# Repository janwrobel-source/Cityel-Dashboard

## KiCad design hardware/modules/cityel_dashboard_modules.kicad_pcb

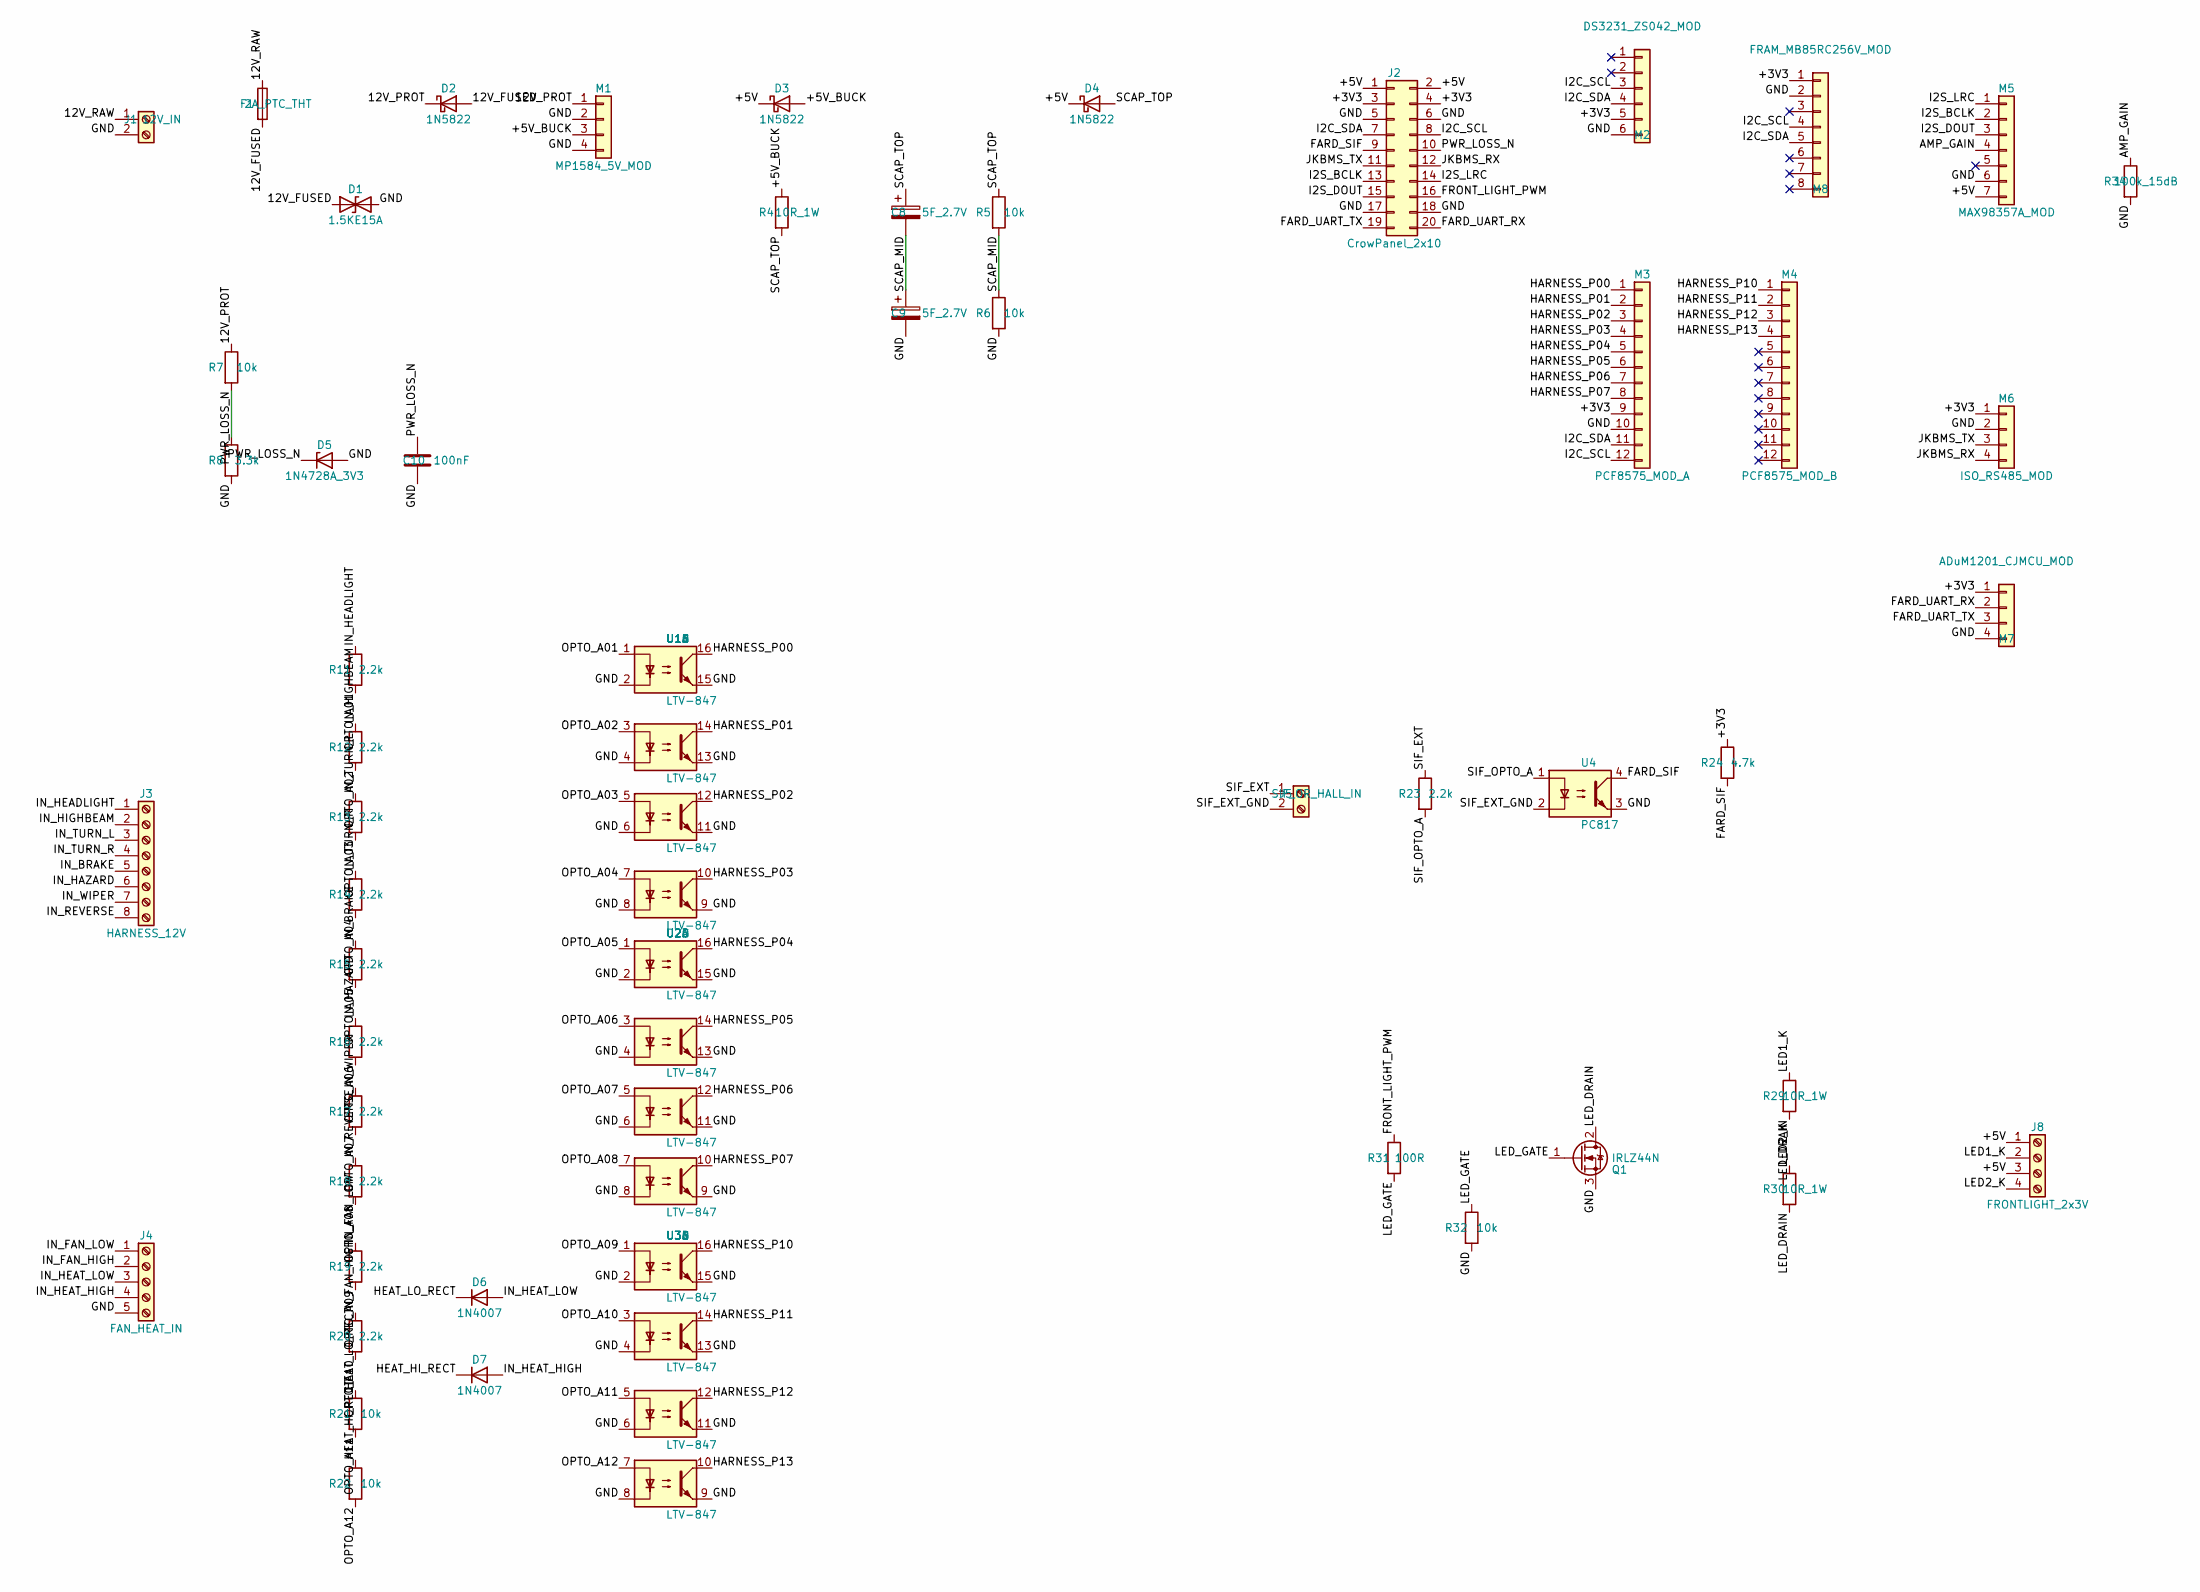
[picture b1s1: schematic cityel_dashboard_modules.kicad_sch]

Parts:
C8, C9: 5F_2.7V; CP_Radial_D10.0mm_P5.00mm
C10: 100nF; C_Disc_D5.0mm_W2.5mm_P5.00mm
D1: 1.5KE15A; D_DO-201AD_P12.70mm_Horizontal
D2, D3, D4: 1N5822; D_DO-201AD_P12.70mm_Horizontal
D5: 1N4728A_3V3; D_DO-41_SOD81_P7.62mm_Horizontal
D6, D7: 1N4007; D_DO-41_SOD81_P7.62mm_Horizontal
F1: 2A_PTC_THT; R_Axial_DIN0207_L6.3mm_D2.5mm_P7.62mm_Horizontal
J1: 12V_IN; TerminalBlock_Phoenix_MKDS-1,5-2-5.08_1x02_P5.08mm_Horizont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
J2: CrowPanel_2x10; PinSocket_2x10_P2.54mm_Vertical
J3: HARNESS_12V; TerminalBlock_Phoenix_MKDS-1,5-8-5.08_1x08_P5.08mm_Horizont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
J4: FAN_HEAT_IN; TerminalBlock_Phoenix_MKDS-1,5-5-5.08_1x05_P5.08mm_Horizont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
J5: SIF_OR_HALL_IN; TerminalBlock_Phoenix_MKDS-1,5-2-5.08_1x02_P5.08mm_Horizont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
J8: FRONTLIGHT_2x3V; TerminalBlock_Phoenix_MKDS-1,5-4-5.08_1x04_P5.08mm_Horizont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
M1: MP1584_5V_MOD; PinSocket_1x04_P2.54mm_Vertical
M2: DS3231_ZS042_MOD; PinSocket_1x06_P2.54mm_Vertical
M3: PCF8575_MOD_A; PinSocket_1x12_P2.54mm_Vertical
M4: PCF8575_MOD_B; PinSocket_1x12_P2.54mm_Vertical
M5: MAX98357A_MOD; PinSocket_1x07_P2.54mm_Vertical
M6: ISO_RS485_MOD; PinSocket_1x04_P2.54mm_Vertical
M7: ADuM1201_CJMCU_MOD; PinSocket_1x04_P2.54mm_Vertical
M8: FRAM_MB85RC256V_MOD; PinSocket_1x08_P2.54mm_Vertical
Q1: IRLZ44N; TO-220-3_Vertical
R4, R29, R30: 10R_1W; R_Axial_DIN0411_L9.9mm_D3.6mm_P12.70mm_Horizontal
R5, R6, R7, R21, R22, R32: 10k; R_Axial_DIN0207_L6.3mm_D2.5mm_P7.62mm_Horizontal
R8: 3.3k; R_Axial_DIN0207_L6.3mm_D2.5mm_P7.62mm_Horizontal
R11, R12, R13, R14, R15, R16, R17, R18, R19, R20, R23: 2.2k; R_Axial_DIN0207_L6.3mm_D2.5mm_P7.62mm_Horizontal
R24: 4.7k; R_Axial_DIN0207_L6.3mm_D2.5mm_P7.62mm_Horizontal
R31: 100R; R_Axial_DIN0207_L6.3mm_D2.5mm_P7.62mm_Horizontal
R34: 100k_15dB; R_Axial_DIN0207_L6.3mm_D2.5mm_P7.62mm_Horizontal
U1, U2, U3: LTV-847; DIP-16_W7.62mm
U4: PC817; DIP-4_W7.62mm

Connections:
/12V_FUSED: D1.1 (A1), D2.2 (A), F1.2
/12V_PROT: D2.1 (K), M1.1, R7.1
/12V_RAW: F1.1, J1.1
/+3V3: J2.3, J2.4, M2.5, M3.9, M6.1, M7.1, M8.1, R24.1
/+5V: D3.1 (K), D4.1 (K), J2.1, J2.2, J8.1, J8.3, M5.7
/+5V_BUCK: D3.2 (A), M1.3, R4.1
/AMP_GAIN: M5.4, R34.1
/FARD_SIF: J2.9, R24.2, U4.4
/FARD_UART_RX: J2.20, M7.2
/FARD_UART_TX: J2.19, M7.3
/FRONT_LIGHT_PWM: J2.16, R31.1
/GND: C9.2, C10.2, D1.2 (A2), D5.2 (A), J1.2, J2.5, J2.6, J2.17, J2.18, J4.5, M1.2, M1.4, M2.6, M3.10, M5.6, M6.2, M7.4, M8.2, Q1.3 (S), R6.2, R8.2, R32.2, R34.2, U1.2, U1.4, U1.6, U1.8, U1.9, U1.11, U1.13, U1.15, U2.2, U2.4, U2.6, U2.8, U2.9, U2.11, U2.13, U2.15, U3.2, U3.4, U3.6, U3.8, U3.9, U3.11, U3.13, U3.15, U4.3
/HARNESS_P00: M3.1, U1.16
/HARNESS_P01: M3.2, U1.14
/HARNESS_P02: M3.3, U1.12
/HARNESS_P03: M3.4, U1.10
/HARNESS_P04: M3.5, U2.16
/HARNESS_P05: M3.6, U2.14
/HARNESS_P06: M3.7, U2.12
/HARNESS_P07: M3.8, U2.10
/HARNESS_P10: M4.1, U3.16
/HARNESS_P11: M4.2, U3.14
/HARNESS_P12: M4.3, U3.12
/HARNESS_P13: M4.4, U3.10
/HEAT_HI_RECT: D7.1 (K), R22.1
/HEAT_LO_RECT: D6.1 (K), R21.1
/I2C_SCL: J2.8, M2.3, M3.12, M8.4
/I2C_SDA: J2.7, M2.4, M3.11, M8.5
/I2S_BCLK: J2.13, M5.2
/I2S_DOUT: J2.15, M5.3
/I2S_LRC: J2.14, M5.1
/IN_BRAKE: J3.5, R15.1
/IN_FAN_HIGH: J4.2, R20.1
/IN_FAN_LOW: J4.1, R19.1
/IN_HAZARD: J3.6, R16.1
/IN_HEADLIGHT: J3.1, R11.1
/IN_HEAT_HIGH: D7.2 (A), J4.4
/IN_HEAT_LOW: D6.2 (A), J4.3
/IN_HIGHBEAM: J3.2, R12.1
/IN_REVERSE: J3.8, R18.1
/IN_TURN_L: J3.3, R13.1
/IN_TURN_R: J3.4, R14.1
/IN_WIPER: J3.7, R17.1
/JKBMS_RX: J2.12, M6.4
/JKBMS_TX: J2.11, M6.3
/LED1_K: J8.2, R29.1
/LED2_K: J8.4, R30.1
/LED_DRAIN: Q1.2 (D), R29.2, R30.2
/LED_GATE: Q1.1 (G), R31.2, R32.1
/OPTO_A01: R11.2, U1.1
/OPTO_A02: R12.2, U1.3
/OPTO_A03: R13.2, U1.5
/OPTO_A04: R14.2, U1.7
/OPTO_A05: R15.2, U2.1
/OPTO_A06: R16.2, U2.3
/OPTO_A07: R17.2, U2.5
/OPTO_A08: R18.2, U2.7
/OPTO_A09: R19.2, U3.1
/OPTO_A10: R20.2, U3.3
/OPTO_A11: R21.2, U3.5
/OPTO_A12: R22.2, U3.7
/PWR_LOSS_N: C10.1, D5.1 (K), J2.10, R7.2, R8.1
/SCAP_MID: C8.2, C9.1, R5.2, R6.1
/SCAP_TOP: C8.1, D4.2 (A), R4.2, R5.1
/SIF_EXT: J5.1, R23.1
/SIF_EXT_GND: J5.2, U4.2
/SIF_OPTO_A: R23.2, U4.1

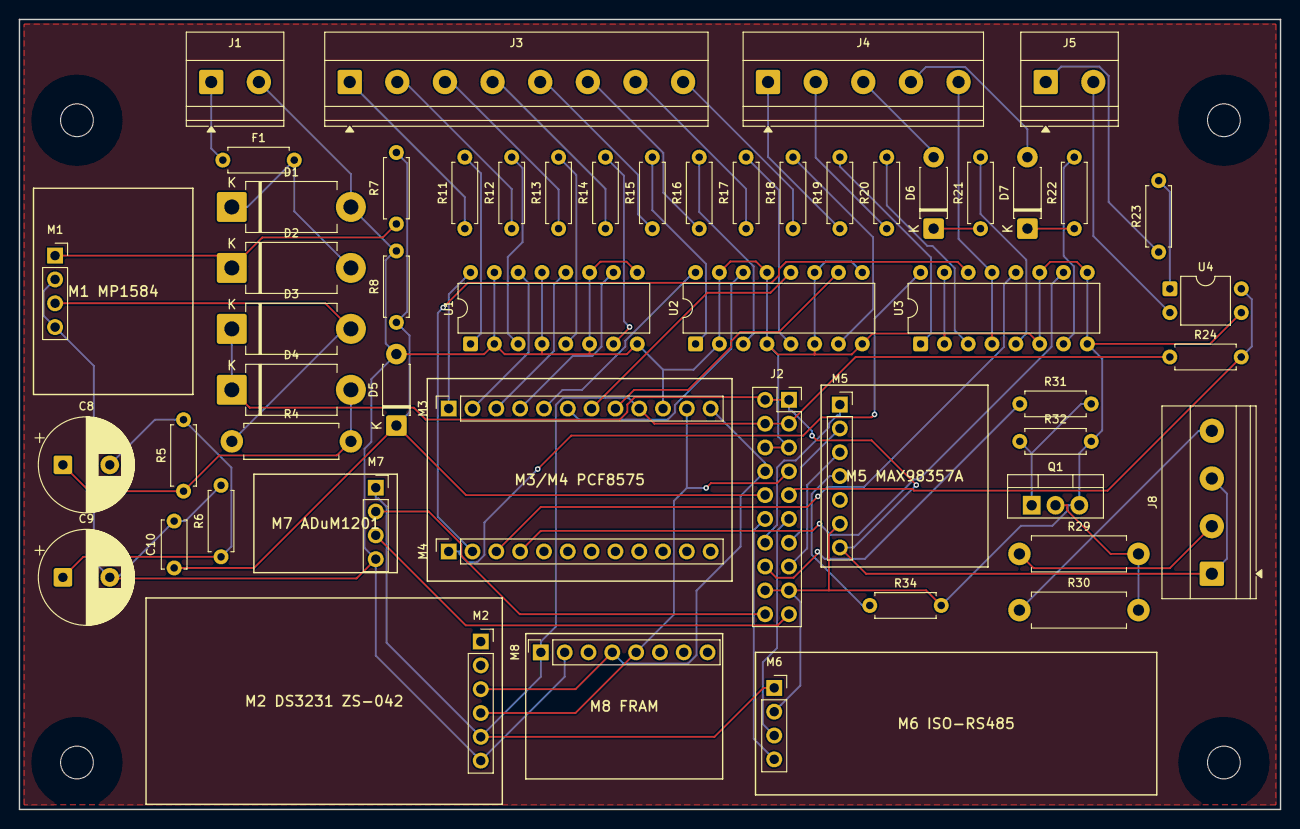
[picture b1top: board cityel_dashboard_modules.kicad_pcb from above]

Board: 2 copper layers, 134.5 x 84.3 mm, 58 parts (0 on the bottom side), 67 nets.

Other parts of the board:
MH1, MH2, MH3, MH4: M3.5; MountingHole_3.5mm

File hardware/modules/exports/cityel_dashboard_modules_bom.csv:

"Refs","Value","Footprint","Qty","DNP"
"C8","5F_2.7V","Capacitor_THT:CP_Radial_D10.0mm_P5.00mm","1",""
"C9","5F_2.7V","Capacitor_THT:CP_Radial_D10.0mm_P5.00mm","1",""
"C10","100nF","Capacitor_THT:C_Disc_D5.0mm_W2.5mm_P5.00mm","1",""
"D1","1.5KE15A","Diode_THT:D_DO-201AD_P12.70mm_Horizontal","1",""
"D2","1N5822","Diode_THT:D_DO-201AD_P12.70mm_Horizontal","1",""
"D3","1N5822","Diode_THT:D_DO-201AD_P12.70mm_Horizontal","1",""
"D4","1N5822","Diode_THT:D_DO-201AD_P12.70mm_Horizontal","1",""
"D5","1N4728A_3V3","Diode_THT:D_DO-41_SOD81_P7.62mm_Horizontal","1",""
"D6","1N4007","Diode_THT:D_DO-41_SOD81_P7.62mm_Horizontal","1",""
"D7","1N4007","Diode_THT:D_DO-41_SOD81_P7.62mm_Horizontal","1",""
"F1","2A_PTC_THT","Resistor_THT:R_Axial_DIN0207_L6.3mm_D2.5mm_P7.62mm_Horizontal","1",""
"J1","12V_IN","TerminalBlock_Phoenix:TerminalBlock_Phoenix_MKDS-1,5-2-5.08_1x02_P5.08mm_Horizontal","1",""
"J2","CrowPanel_2x10","Connector_PinSocket_2.54mm:PinSocket_2x10_P2.54mm_Vertical","1",""
"J3","HARNESS_12V","TerminalBlock_Phoenix:TerminalBlock_Phoenix_MKDS-1,5-8-5.08_1x08_P5.08mm_Horizontal","1",""
"J4","FAN_HEAT_IN","TerminalBlock_Phoenix:TerminalBlock_Phoenix_MKDS-1,5-5-5.08_1x05_P5.08mm_Horizontal","1",""
"J5","SIF_OR_HALL_IN","TerminalBlock_Phoenix:TerminalBlock_Phoenix_MKDS-1,5-2-5.08_1x02_P5.08mm_Horizontal","1",""
"J8","FRONTLIGHT_2x3V","TerminalBlock_Phoenix:TerminalBlock_Phoenix_MKDS-1,5-4-5.08_1x04_P5.08mm_Horizontal","1",""
"M1","MP1584_5V_MOD","Connector_PinSocket_2.54mm:PinSocket_1x04_P2.54mm_Vertical","1",""
"M2","DS3231_ZS042_MOD","Connector_PinSocket_2.54mm:PinSocket_1x06_P2.54mm_Vertical","1",""
"M3","PCF8575_MOD_A","Connector_PinSocket_2.54mm:PinSocket_1x12_P2.54mm_Vertical","1",""
"M4","PCF8575_MOD_B","Connector_PinSocket_2.54mm:PinSocket_1x12_P2.54mm_Vertical","1",""
"M5","MAX98357A_MOD","Connector_PinSocket_2.54mm:PinSocket_1x07_P2.54mm_Vertical","1",""
"M6","ISO_RS485_MOD","Connector_PinSocket_2.54mm:PinSocket_1x04_P2.54mm_Vertical","1",""
"M7","ADuM1201_CJMCU_MOD","Connector_PinSocket_2.54mm:PinSocket_1x04_P2.54mm_Vertical","1",""
"M8","FRAM_MB85RC256V_MOD","Connector_PinSocket_2.54mm:PinSocket_1x08_P2.54mm_Vertical","1",""
"Q1","IRLZ44N","Package_TO_SOT_THT:TO-220-3_Vertical","1",""
"R4","10R_1W","Resistor_THT:R_Axial_DIN0411_L9.9mm_D3.6mm_P12.70mm_Horizontal","1",""
"R5","10k","Resistor_THT:R_Axial_DIN0207_L6.3mm_D2.5mm_P7.62mm_Horizontal","1",""
"R6","10k","Resistor_THT:R_Axial_DIN0207_L6.3mm_D2.5mm_P7.62mm_Horizontal","1",""
"R7","10k","Resistor_THT:R_Axial_DIN0207_L6.3mm_D2.5mm_P7.62mm_Horizontal","1",""
"R8","3.3k","Resistor_THT:R_Axial_DIN0207_L6.3mm_D2.5mm_P7.62mm_Horizontal","1",""
"R11","2.2k","Resistor_THT:R_Axial_DIN0207_L6.3mm_D2.5mm_P7.62mm_Horizontal","1",""
"R12","2.2k","Resistor_THT:R_Axial_DIN0207_L6.3mm_D2.5mm_P7.62mm_Horizontal","1",""
"R13","2.2k","Resistor_THT:R_Axial_DIN0207_L6.3mm_D2.5mm_P7.62mm_Horizontal","1",""
"R14","2.2k","Resistor_THT:R_Axial_DIN0207_L6.3mm_D2.5mm_P7.62mm_Horizontal","1",""
"R15","2.2k","Resistor_THT:R_Axial_DIN0207_L6.3mm_D2.5mm_P7.62mm_Horizontal","1",""
"R16","2.2k","Resistor_THT:R_Axial_DIN0207_L6.3mm_D2.5mm_P7.62mm_Horizontal","1",""
"R17","2.2k","Resistor_THT:R_Axial_DIN0207_L6.3mm_D2.5mm_P7.62mm_Horizontal","1",""
"R18","2.2k","Resistor_THT:R_Axial_DIN0207_L6.3mm_D2.5mm_P7.62mm_Horizontal","1",""
"R19","2.2k","Resistor_THT:R_Axial_DIN0207_L6.3mm_D2.5mm_P7.62mm_Horizontal","1",""
"R20","2.2k","Resistor_THT:R_Axial_DIN0207_L6.3mm_D2.5mm_P7.62mm_Horizontal","1",""
"R21","10k","Resistor_THT:R_Axial_DIN0207_L6.3mm_D2.5mm_P7.62mm_Horizontal","1",""
"R22","10k","Resistor_THT:R_Axial_DIN0207_L6.3mm_D2.5mm_P7.62mm_Horizontal","1",""
"R23","2.2k","Resistor_THT:R_Axial_DIN0207_L6.3mm_D2.5mm_P7.62mm_Horizontal","1",""
"R24","4.7k","Resistor_THT:R_Axial_DIN0207_L6.3mm_D2.5mm_P7.62mm_Horizontal","1",""
"R29","10R_1W","Resistor_THT:R_Axial_DIN0411_L9.9mm_D3.6mm_P12.70mm_Horizontal","1",""
"R30","10R_1W","Resistor_THT:R_Axial_DIN0411_L9.9mm_D3.6mm_P12.70mm_Horizontal","1",""
"R31","100R","Resistor_THT:R_Axial_DIN0207_L6.3mm_D2.5mm_P7.62mm_Horizontal","1",""
"R32","10k","Resistor_THT:R_Axial_DIN0207_L6.3mm_D2.5mm_P7.62mm_Horizontal","1",""
"R34","100k_15dB","Resistor_THT:R_Axial_DIN0207_L6.3mm_D2.5mm_P7.62mm_Horizontal","1",""
"U1","LTV-847","Package_DIP:DIP-16_W7.62mm","1",""
"U2","LTV-847","Package_DIP:DIP-16_W7.62mm","1",""
"U3","LTV-847","Package_DIP:DIP-16_W7.62mm","1",""
"U4","PC817","Package_DIP:DIP-4_W7.62mm","1",""

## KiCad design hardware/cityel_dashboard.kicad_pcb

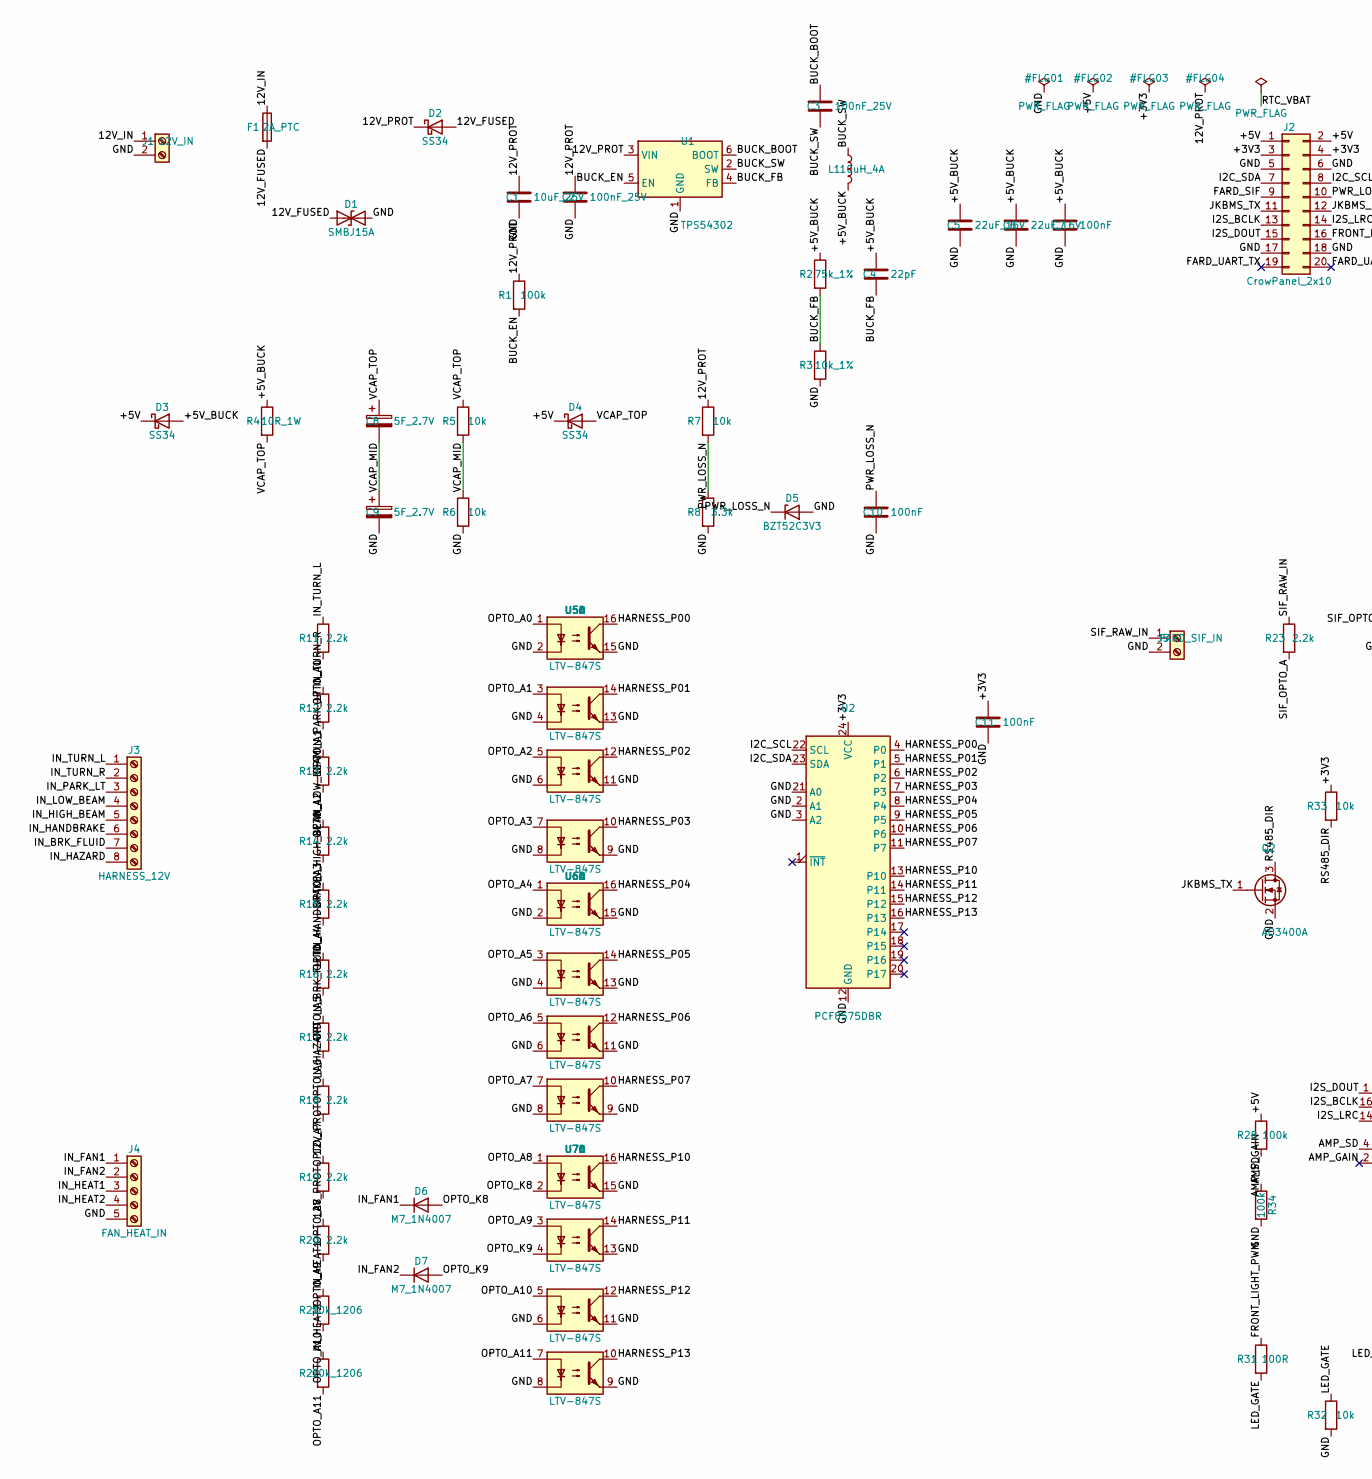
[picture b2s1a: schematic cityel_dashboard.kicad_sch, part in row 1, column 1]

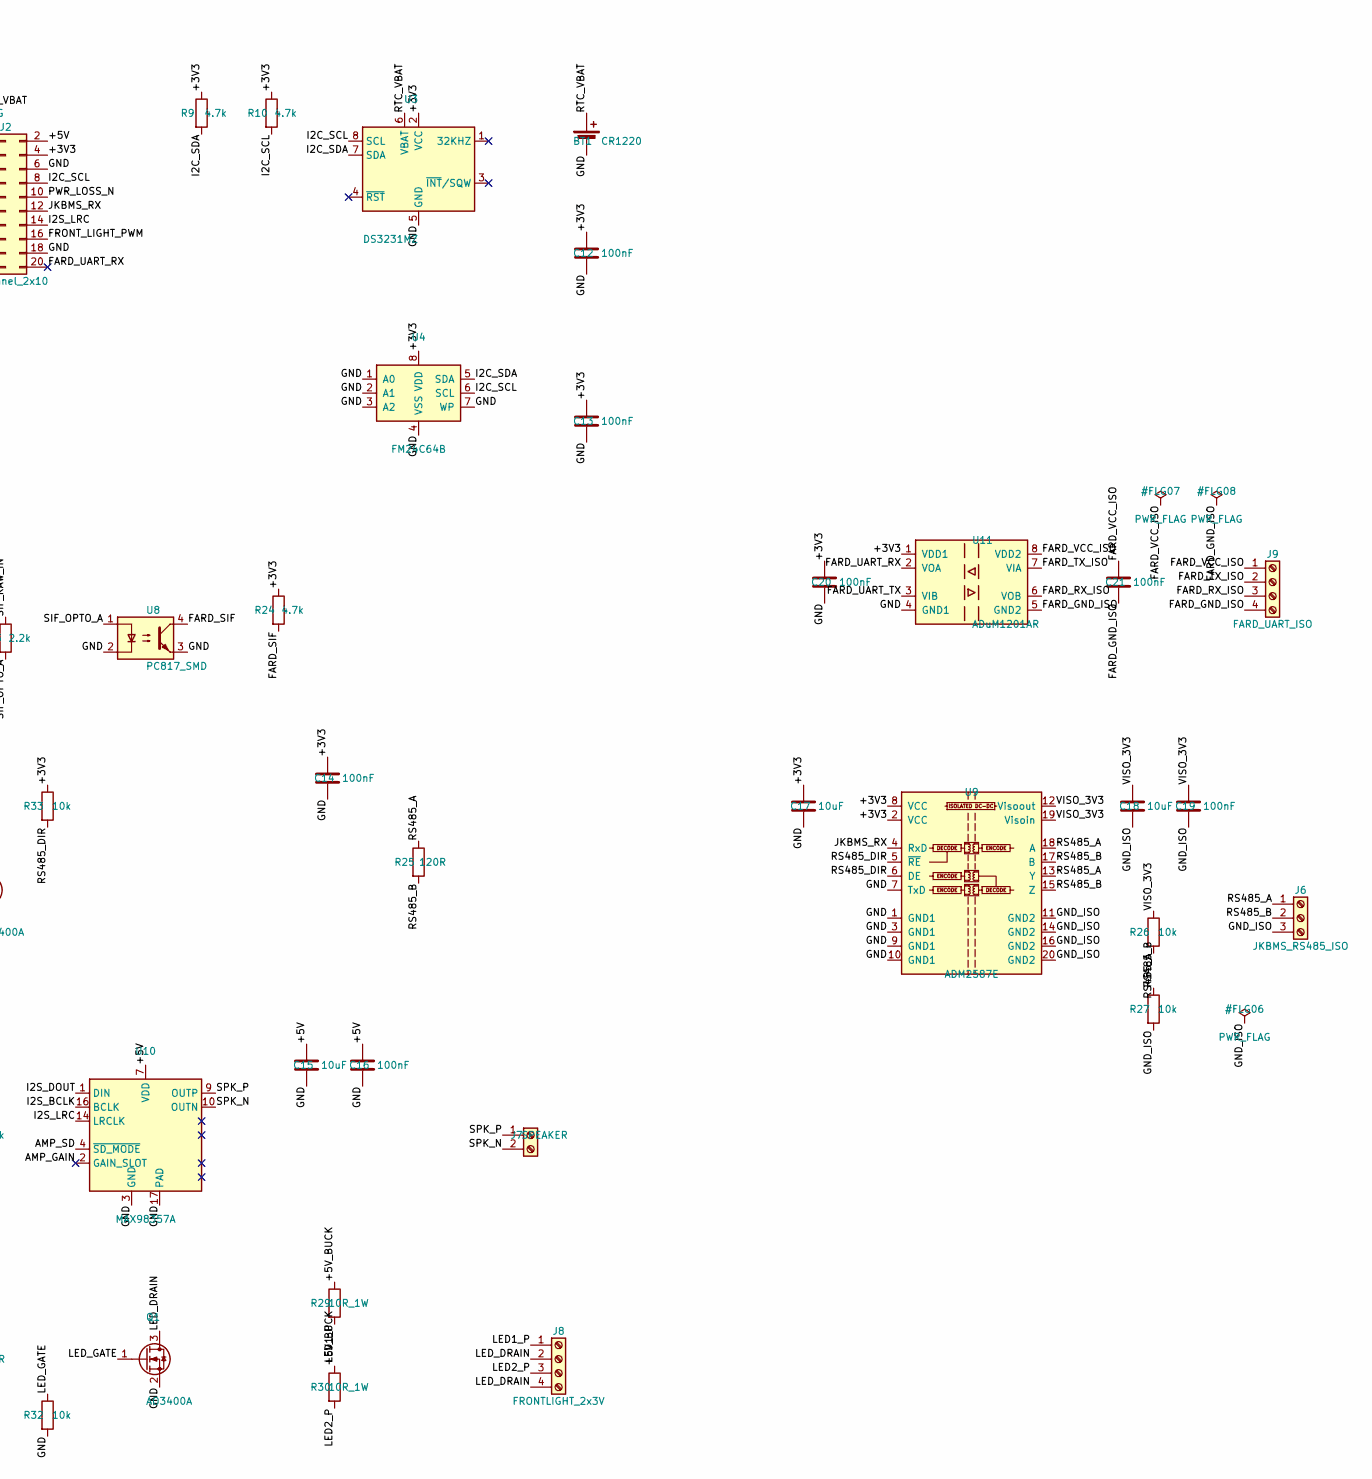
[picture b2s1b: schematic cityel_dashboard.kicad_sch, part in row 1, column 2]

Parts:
BT1: CR1220; BatteryHolder_Keystone_3000_1x12mm
C1: 10uF_25V; C_0805_2012Metric
C2, C3: 100nF_25V; C_0603_1608Metric
C4: 22pF; C_0603_1608Metric
C5, C6: 22uF_16V; C_0805_2012Metric
C7, C10, C11, C12, C13, C14, C16, C19, C20, C21: 100nF; C_0603_1608Metric
C8, C9: 5F_2.7V; CP_Radial_D10.0mm_P5.00mm
C15, C17, C18: 10uF; C_0805_2012Metric
D1: SMBJ15A; D_SMB
D2, D3, D4: SS34; D_SMA
D5: BZT52C3V3; D_SOD-123
D6, D7: M7_1N4007; D_SMA
F1: 2A_PTC; Fuse_1812_4532Metric
J1: 12V_IN; TerminalBlock_Phoenix_MKDS-1,5-2-5.08_1x02_P5.08mm_Horizont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
J2: CrowPanel_2x10; PinSocket_2x10_P2.54mm_Vertical
J3: HARNESS_12V; TerminalBlock_Phoenix_MKDS-1,5-8-5.08_1x08_P5.08mm_Horizont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
J4: FAN_HEAT_IN; TerminalBlock_Phoenix_MKDS-1,5-5-5.08_1x05_P5.08mm_Horizont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
J5: FARD_SIF_IN; TerminalBlock_Phoenix_MKDS-1,5-2-5.08_1x02_P5.08mm_Horizont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
J6: JKBMS_RS485_ISO; TerminalBlock_Phoenix_MKDS-1,5-3-5.08_1x03_P5.08mm_Horizont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
J7: SPEAKER; TerminalBlock_Phoenix_MKDS-1,5-2-5.08_1x02_P5.08mm_Horizont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
J8: FRONTLIGHT_2x3V; TerminalBlock_Phoenix_MKDS-1,5-4-5.08_1x04_P5.08mm_Horizont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
J9: FARD_UART_ISO; TerminalBlock_Phoenix_MKDS-1,5-4-5.08_1x04_P5.08mm_Horizont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
L1: 10uH_4A; L_Bourns_SRR1260
Q1, Q2: AO3400A; SOT-23
R1, R28, R34: 100k; R_0603_1608Metric
R2: 75k_1%; R_0603_1608Metric
R3: 10k_1%; R_0603_1608Metric
R4, R29, R30: 10R_1W; R_2512_6332Metric
R5, R6, R7, R26, R27, R32, R33: 10k; R_0603_1608Metric
R8: 3.3k; R_0603_1608Metric
R9, R10, R24: 4.7k; R_0603_1608Metric
R11, R12, R13, R14, R15, R16, R17, R18, R19, R20, R23: 2.2k; R_0805_2012Metric
R21, R22: 10k_1206; R_1206_3216Metric
R25: 120R; R_0603_1608Metric
R31: 100R; R_0603_1608Metric
U1: TPS54302; SOT-23-6
U2: PCF8575DBR; SSOP-24_5.3x8.2mm_P0.65mm
U3: DS3231MZ; SOIC-8_3.9x4.9mm_P1.27mm
U4: FM24C64B; SOIC-8_3.9x4.9mm_P1.27mm
U5, U6, U7: LTV-847S; SMDIP-16_W9.53mm
U8: PC817_SMD; SMDIP-4_W9.53mm
U9: ADM2587E; SOIC-20W_7.5x12.8mm_P1.27mm
U10: MAX98357A; TQFN-16-1EP_3x3mm_P0.5mm_EP1.6x1.6mm
U11: ADuM1201AR; SOIC-8_3.9x4.9mm_P1.27mm

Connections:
/12V_FUSED: D1.1 (A1), D2.2 (A), F1.2
/12V_IN: F1.1, J1.1
/12V_PROT: C1.1, C2.1, D2.1 (K), R1.1, R7.1, R19.1, R20.1, U1.3 (VIN)
/+3V3: C11.1, C12.1, C13.1, C14.1, C17.1, C20.1, J2.3, J2.4, R9.1, R10.1, R24.1, R33.1, U2.24 (VCC), U3.2 (VCC), U4.8 (VDD), U9.2 (VCC), U9.8 (VCC), U11.1 (VDD1)
/+5V: C15.1, C16.1, D3.1 (K), D4.1 (K), J2.1, J2.2, R28.1, U10.7 (VDD), U10.8 (VDD)
/+5V_BUCK: C4.1, C5.1, C6.1, C7.1, D3.2 (A), L1.2, R2.1, R4.1, R29.1, R30.1
/AMP_GAIN: R34.1, U10.2 (GAIN_SLOT)
/AMP_SD: R28.2, U10.4 (~SD_MODE)
/BUCK_BOOT: C3.1, U1.6 (BOOT)
/BUCK_EN: R1.2, U1.5 (EN)
/BUCK_FB: C4.2, R2.2, R3.1, U1.4 (FB)
/BUCK_SW: C3.2, L1.1, U1.2 (SW)
/FARD_GND_ISO: C21.2, J9.4, U11.5 (GND2)
/FARD_RX_ISO: J9.3, U11.6 (VOB)
/FARD_SIF: J2.9, R24.2, U8.4
/FARD_TX_ISO: J9.2, U11.7 (VIA)
/FARD_UART_RX: J2.20, U11.2 (VOA)
/FARD_UART_TX: J2.19, U11.3 (VIB)
/FARD_VCC_ISO: C21.1, J9.1, U11.8 (VDD2)
/FRONT_LIGHT_PWM: J2.16, R31.1
/GND: BT1.2 (-), C1.2, C2.2, C5.2, C6.2, C7.2, C9.2, C10.2, C11.2, C12.2, C13.2, C14.2, C15.2, C16.2, C17.2, C20.2, D1.2 (A2), D5.2 (A), J1.2, J2.5, J2.6, J2.17, J2.18, J4.5, J5.2, Q1.2 (S), Q2.2 (S), R3.2, R6.2, R8.2, R32.2, R34.2, U1.1 (GND), U2.2 (A1), U2.3 (A2), U2.12 (GND), U2.21 (A0), U3.5 (GND), U4.1 (A0), U4.2 (A1), U4.3 (A2), U4.4 (VSS), U4.7 (WP), U5.2, U5.4, U5.6, U5.8, U5.9, U5.11, U5.13, U5.15, U6.2, U6.4, U6.6, U6.8, U6.9, U6.11, U6.13, U6.15, U7.6, U7.8, U7.9, U7.11, U7.13, U7.15, U8.2, U8.3, U9.1 (GND1), U9.3 (GND1), U9.7 (TxD), U9.9 (GND1), U9.10 (GND1), U10.3 (GND), U10.11 (GND), U10.15 (GND), U10.17 (PAD), U11.4 (GND1)
/GND_ISO: C18.2, C19.2, J6.3, R27.2, U9.11 (GND2), U9.14 (GND2), U9.16 (GND2), U9.20 (GND2)
/HARNESS_P00: U2.4 (P0), U5.16
/HARNESS_P01: U2.5 (P1), U5.14
/HARNESS_P02: U2.6 (P2), U5.12
/HARNESS_P03: U2.7 (P3), U5.10
/HARNESS_P04: U2.8 (P4), U6.16
/HARNESS_P05: U2.9 (P5), U6.14
/HARNESS_P06: U2.10 (P6), U6.12
/HARNESS_P07: U2.11 (P7), U6.10
/HARNESS_P10: U2.13 (P10), U7.16
/HARNESS_P11: U2.14 (P11), U7.14
/HARNESS_P12: U2.15 (P12), U7.12
/HARNESS_P13: U2.16 (P13), U7.10
/I2C_SCL: J2.8, R10.2, U2.22 (SCL), U3.8 (SCL), U4.6 (SCL)
/I2C_SDA: J2.7, R9.2, U2.23 (SDA), U3.7 (SDA), U4.5 (SDA)
/I2S_BCLK: J2.13, U10.16 (BCLK)
/I2S_DOUT: J2.15, U10.1 (DIN)
/I2S_LRC: J2.14, U10.14 (LRCLK)
/IN_BRK_FLUID: J3.7, R17.1
/IN_FAN1: D6.1 (K), J4.1
/IN_FAN2: D7.1 (K), J4.2
/IN_HANDBRAKE: J3.6, R16.1
/IN_HAZARD: J3.8, R18.1
/IN_HEAT1: J4.3, R21.1
/IN_HEAT2: J4.4, R22.1
/IN_HIGH_BEAM: J3.5, R15.1
/IN_LOW_BEAM: J3.4, R14.1
/IN_PARK_LT: J3.3, R13.1
/IN_TURN_L: J3.1, R11.1
/IN_TURN_R: J3.2, R12.1
/JKBMS_RX: J2.12, U9.4 (RxD)
/JKBMS_TX: J2.11, Q2.1 (G)
/LED1_P: J8.1, R29.2
/LED2_P: J8.3, R30.2
/LED_DRAIN: J8.2, J8.4, Q1.3 (D)
/LED_GATE: Q1.1 (G), R31.2, R32.1
/OPTO_A0: R11.2, U5.1
/OPTO_A1: R12.2, U5.3
/OPTO_A2: R13.2, U5.5
/OPTO_A3: R14.2, U5.7
/OPTO_A4: R15.2, U6.1
/OPTO_A5: R16.2, U6.3
/OPTO_A6: R17.2, U6.5
/OPTO_A7: R18.2, U6.7
/OPTO_A8: R19.2, U7.1
/OPTO_A9: R20.2, U7.3
/OPTO_A10: R21.2, U7.5
/OPTO_A11: R22.2, U7.7
/OPTO_K8: D6.2 (A), U7.2
/OPTO_K9: D7.2 (A), U7.4
/PWR_LOSS_N: C10.1, D5.1 (K), J2.10, R7.2, R8.1
/RS485_A: J6.1, R25.1, R26.2, U9.13 (Y), U9.18 (A)
/RS485_B: J6.2, R25.2, R27.1, U9.15 (Z), U9.17 (B)
/RS485_DIR: Q2.3 (D), R33.2, U9.5 (~RE), U9.6 (DE)
/RTC_VBAT: BT1.1 (+), U3.6 (VBAT)
/SIF_OPTO_A: R23.2, U8.1
/SIF_RAW_IN: J5.1, R23.1
/SPK_N: J7.2, U10.10 (OUTN)
/SPK_P: J7.1, U10.9 (OUTP)
/VCAP_MID: C8.2, C9.1, R5.2, R6.1
/VCAP_TOP: C8.1, D4.2 (A), R4.2, R5.1
/VISO_3V3: C18.1, C19.1, R26.1, U9.12 (Visoout), U9.19 (Visoin)

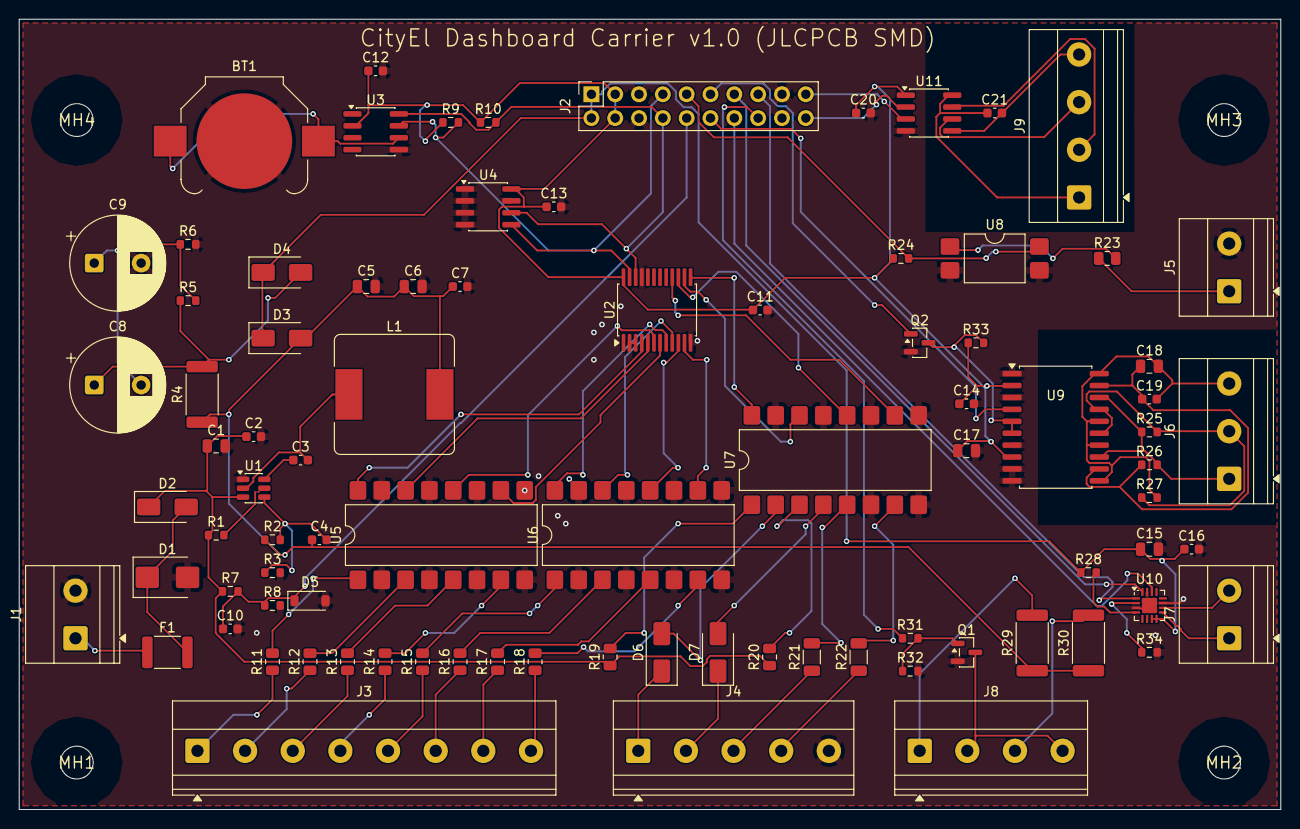
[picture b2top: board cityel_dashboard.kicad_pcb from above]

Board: 2 copper layers, 134.5 x 84.3 mm, 91 parts (0 on the bottom side), 83 nets.

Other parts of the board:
MH1, MH3, MH4: MountingHole_3.5mm
MH2: MountingHole_4.5mm

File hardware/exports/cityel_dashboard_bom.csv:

"Refs","Value","Footprint","Qty","DNP"
"BT1","CR1220","Battery:BatteryHolder_Keystone_3000_1x12mm","1",""
"C1","10uF_25V","Capacitor_SMD:C_0805_2012Metric","1",""
"C2","100nF_25V","Capacitor_SMD:C_0603_1608Metric","1",""
"C3","100nF_25V","Capacitor_SMD:C_0603_1608Metric","1",""
"C4","22pF","Capacitor_SMD:C_0603_1608Metric","1",""
"C5","22uF_16V","Capacitor_SMD:C_0805_2012Metric","1",""
"C6","22uF_16V","Capacitor_SMD:C_0805_2012Metric","1",""
"C7","100nF","Capacitor_SMD:C_0603_1608Metric","1",""
"C8","5F_2.7V","Capacitor_THT:CP_Radial_D10.0mm_P5.00mm","1",""
"C9","5F_2.7V","Capacitor_THT:CP_Radial_D10.0mm_P5.00mm","1",""
"C10","100nF","Capacitor_SMD:C_0603_1608Metric","1",""
"C11","100nF","Capacitor_SMD:C_0603_1608Metric","1",""
"C12","100nF","Capacitor_SMD:C_0603_1608Metric","1",""
"C13","100nF","Capacitor_SMD:C_0603_1608Metric","1",""
"C14","100nF","Capacitor_SMD:C_0603_1608Metric","1",""
"C15","10uF","Capacitor_SMD:C_0805_2012Metric","1",""
"C16","100nF","Capacitor_SMD:C_0603_1608Metric","1",""
"C17","10uF","Capacitor_SMD:C_0805_2012Metric","1",""
"C18","10uF","Capacitor_SMD:C_0805_2012Metric","1",""
"C19","100nF","Capacitor_SMD:C_0603_1608Metric","1",""
"C20","100nF","Capacitor_SMD:C_0603_1608Metric","1",""
"C21","100nF","Capacitor_SMD:C_0603_1608Metric","1",""
"D1","SMBJ15A","Diode_SMD:D_SMB","1",""
"D2","SS34","Diode_SMD:D_SMA","1",""
"D3","SS34","Diode_SMD:D_SMA","1",""
"D4","SS34","Diode_SMD:D_SMA","1",""
"D5","BZT52C3V3","Diode_SMD:D_SOD-123","1",""
"D6","M7_1N4007","Diode_SMD:D_SMA","1",""
"D7","M7_1N4007","Diode_SMD:D_SMA","1",""
"F1","2A_PTC","Fuse:Fuse_1812_4532Metric","1",""
"J1","12V_IN","TerminalBlock_Phoenix:TerminalBlock_Phoenix_MKDS-1,5-2-5.08_1x02_P5.08mm_Horizontal","1",""
"J2","CrowPanel_2x10","Connector_PinSocket_2.54mm:PinSocket_2x10_P2.54mm_Vertical","1",""
"J3","HARNESS_12V","TerminalBlock_Phoenix:TerminalBlock_Phoenix_MKDS-1,5-8-5.08_1x08_P5.08mm_Horizontal","1",""
"J4","FAN_HEAT_IN","TerminalBlock_Phoenix:TerminalBlock_Phoenix_MKDS-1,5-5-5.08_1x05_P5.08mm_Horizontal","1",""
"J5","FARD_SIF_IN","TerminalBlock_Phoenix:TerminalBlock_Phoenix_MKDS-1,5-2-5.08_1x02_P5.08mm_Horizontal","1",""
"J6","JKBMS_RS485_ISO","TerminalBlock_Phoenix:TerminalBlock_Phoenix_MKDS-1,5-3-5.08_1x03_P5.08mm_Horizontal","1",""
"J7","SPEAKER","TerminalBlock_Phoenix:TerminalBlock_Phoenix_MKDS-1,5-2-5.08_1x02_P5.08mm_Horizontal","1",""
"J8","FRONTLIGHT_2x3V","TerminalBlock_Phoenix:TerminalBlock_Phoenix_MKDS-1,5-4-5.08_1x04_P5.08mm_Horizontal","1",""
"J9","FARD_UART_ISO","TerminalBlock_Phoenix:TerminalBlock_Phoenix_MKDS-1,5-4-5.08_1x04_P5.08mm_Horizontal","1",""
"L1","10uH_4A","Inductor_SMD:L_Bourns_SRR1260","1",""
"Q1","AO3400A","Package_TO_SOT_SMD:SOT-23","1",""
"Q2","AO3400A","Package_TO_SOT_SMD:SOT-23","1",""
"R1","100k","Resistor_SMD:R_0603_1608Metric","1",""
"R2","75k_1%","Resistor_SMD:R_0603_1608Metric","1",""
"R3","10k_1%","Resistor_SMD:R_0603_1608Metric","1",""
"R4","10R_1W","Resistor_SMD:R_2512_6332Metric","1",""
"R5","10k","Resistor_SMD:R_0603_1608Metric","1",""
"R6","10k","Resistor_SMD:R_0603_1608Metric","1",""
"R7","10k","Resistor_SMD:R_0603_1608Metric","1",""
"R8","3.3k","Resistor_SMD:R_0603_1608Metric","1",""
"R9","4.7k","Resistor_SMD:R_0603_1608Metric","1",""
"R10","4.7k","Resistor_SMD:R_0603_1608Metric","1",""
"R11","2.2k","Resistor_SMD:R_0805_2012Metric","1",""
"R12","2.2k","Resistor_SMD:R_0805_2012Metric","1",""
"R13","2.2k","Resistor_SMD:R_0805_2012Metric","1",""
"R14","2.2k","Resistor_SMD:R_0805_2012Metric","1",""
"R15","2.2k","Resistor_SMD:R_0805_2012Metric","1",""
"R16","2.2k","Resistor_SMD:R_0805_2012Metric","1",""
"R17","2.2k","Resistor_SMD:R_0805_2012Metric","1",""
"R18","2.2k","Resistor_SMD:R_0805_2012Metric","1",""
"R19","2.2k","Resistor_SMD:R_0805_2012Metric","1",""
"R20","2.2k","Resistor_SMD:R_0805_2012Metric","1",""
"R21","10k_1206","Resistor_SMD:R_1206_3216Metric","1",""
"R22","10k_1206","Resistor_SMD:R_1206_3216Metric","1",""
"R23","2.2k","Resistor_SMD:R_0805_2012Metric","1",""
"R24","4.7k","Resistor_SMD:R_0603_1608Metric","1",""
"R25","120R","Resistor_SMD:R_0603_1608Metric","1",""
"R26","10k","Resistor_SMD:R_0603_1608Metric","1",""
"R27","10k","Resistor_SMD:R_0603_1608Metric","1",""
"R28","100k","Resistor_SMD:R_0603_1608Metric","1",""
"R29","10R_1W","Resistor_SMD:R_2512_6332Metric","1",""
"R30","10R_1W","Resistor_SMD:R_2512_6332Metric","1",""
"R31","100R","Resistor_SMD:R_0603_1608Metric","1",""
"R32","10k","Resistor_SMD:R_0603_1608Metric","1",""
"R33","10k","Resistor_SMD:R_0603_1608Metric","1",""
"R34","100k","Resistor_SMD:R_0603_1608Metric","1",""
"U1","TPS54302","Package_TO_SOT_SMD:SOT-23-6","1",""
"U2","PCF8575DBR","Package_SO:SSOP-24_5.3x8.2mm_P0.65mm","1",""
"U3","DS3231MZ","Package_SO:SOIC-8_3.9x4.9mm_P1.27mm","1",""
"U4","FM24C64B","Package_SO:SOIC-8_3.9x4.9mm_P1.27mm","1",""
"U5","LTV-847S","Package_DIP:SMDIP-16_W9.53mm","1",""
"U6","LTV-847S","Package_DIP:SMDIP-16_W9.53mm","1",""
"U7","LTV-847S","Package_DIP:SMDIP-16_W9.53mm","1",""
"U8","PC817_SMD","Package_DIP:SMDIP-4_W9.53mm","1",""
"U9","ADM2587E","Package_SO:SOIC-20W_7.5x12.8mm_P1.27mm","1",""
"U10","MAX98357A","Package_DFN_QFN:TQFN-16-1EP_3x3mm_P0.5mm_EP1.6x1.6mm","1",""
"U11","ADuM1201AR","Package_SO:SOIC-8_3.9x4.9mm_P1.27mm","1",""

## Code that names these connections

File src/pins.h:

#pragma once

#include <stdint.h>

// --- 1. CrowPanel ESP32-S3 5.79" E-Paper Display (SPI) ---
constexpr uint8_t EPD_MOSI_PIN = 11;
constexpr uint8_t EPD_SCK_PIN  = 12;
constexpr uint8_t EPD_CS_PIN   = 45;
constexpr uint8_t EPD_DC_PIN   = 46;
constexpr uint8_t EPD_RST_PIN  = 47;
constexpr uint8_t EPD_BUSY_PIN = 48;
constexpr uint8_t EPD_PWR_PIN  = 7;   // Powers on the E-Ink screen 3.3V rail

// --- 2. Onboard Buttons & Rocker Switch ---
constexpr uint8_t BTN_EXIT_PIN = 1;
constexpr uint8_t BTN_MENU_PIN = 2;
constexpr uint8_t BTN_DOWN_PIN = 4;
constexpr uint8_t BTN_CONF_PIN = 5;   // Rotary/rocker switch press (CONF)
constexpr uint8_t BTN_UP_PIN   = 6;

// --- 3. I2C Bus & Device Addresses ---
constexpr uint8_t I2C_SDA_PIN       = 19;
constexpr uint8_t I2C_SCL_PIN       = 20;
constexpr uint8_t EXPANDER_I2C_ADDR = 0x20; // PCF8575 / TCA9555 / MCP23017 Harness IO
constexpr uint8_t ODO_FRAM_I2C_ADDR = 0x51; // I2C FRAM (Odometer storage)
constexpr uint8_t DS3231_I2C_ADDR   = 0x68; // DS3231 Real-Time Clock

// --- 4. FarDriver Controller (One-LIN / SIF Input + Isolated UART2) ---
constexpr uint8_t FARD_SIF_PIN     = 15;
constexpr uint8_t FARD_UART_TX_PIN = 3;   // Isolated UART2 TX -> FarDriver RX (ADuM1201)
constexpr uint8_t FARD_UART_RX_PIN = 21;  // Isolated UART2 RX <- FarDriver TX (ADuM1201)

// --- 5. JK-BMS (RS485 UART1 / CAN TWAI) ---
constexpr uint8_t JKBMS_TX_PIN = 17;
constexpr uint8_t JKBMS_RX_PIN = 18;

// --- 6. MAX98357A I2S Audio Amplifier ---
constexpr uint8_t I2S_BCLK_PIN = 38;
constexpr uint8_t I2S_LRC_PIN  = 8;
constexpr uint8_t I2S_DOUT_PIN = 16;

// --- 7. Panel Front Lighting (PWM LED) & Power Loss Sense ---
constexpr uint8_t FRONT_LIGHT_PIN = 14;
constexpr uint8_t PWR_LOSS_PIN    = 9;   // Active-LOW upstream 12V power-loss sense (20-pin header IO9, RTC-wake capable)

// --- 8. PCF8575 / TCA9555 I2C Expander Optocoupler Input Bits ---
constexpr uint8_t HARNESS_BIT_TURN_LEFT   = 0;  // P00 <- J4-1  (SW-WS, +12V active)
constexpr uint8_t HARNESS_BIT_TURN_RIGHT  = 1;  // P01 <- J3-7  (GN-SW, +12V active)
constexpr uint8_t HARNESS_BIT_PARKING_LT  = 2;  // P02 <- J3-15 (GR,    +12V active)
constexpr uint8_t HARNESS_BIT_LOW_BEAM    = 3;  // P03 <- J22-2 (GE,    +12V active)
constexpr uint8_t HARNESS_BIT_HIGH_BEAM   = 4;  // P04 <- J3-9  (WS,    +12V active)
constexpr uint8_t HARNESS_BIT_HANDBRAKE   = 5;  // P05 <- J4-3  (RT-WS, +12V active)
constexpr uint8_t HARNESS_BIT_BRAKE_FLUID = 6;  // P06 <- J4-2  (GE-BR, +12V active)
constexpr uint8_t HARNESS_BIT_HAZARD      = 7;  // P07 <- J3-8  (SW-RT, +12V active)
constexpr uint8_t HARNESS_BIT_FAN_1       = 8;  // P10 <- J3-10 (BR-RT, 0V active-LOW + 1N4007 block)
constexpr uint8_t HARNESS_BIT_FAN_2       = 9;  // P11 <- S3-11 (BL-GE, 0V active-LOW + 1N4007 block)
constexpr uint8_t HARNESS_BIT_HEAT_1      = 10; // P12 <- J3-12 (GN-WS, +36V/Pack active)
constexpr uint8_t HARNESS_BIT_HEAT_2      = 11; // P13 <- J3-11 (GR-WS, +36V/Pack active)
